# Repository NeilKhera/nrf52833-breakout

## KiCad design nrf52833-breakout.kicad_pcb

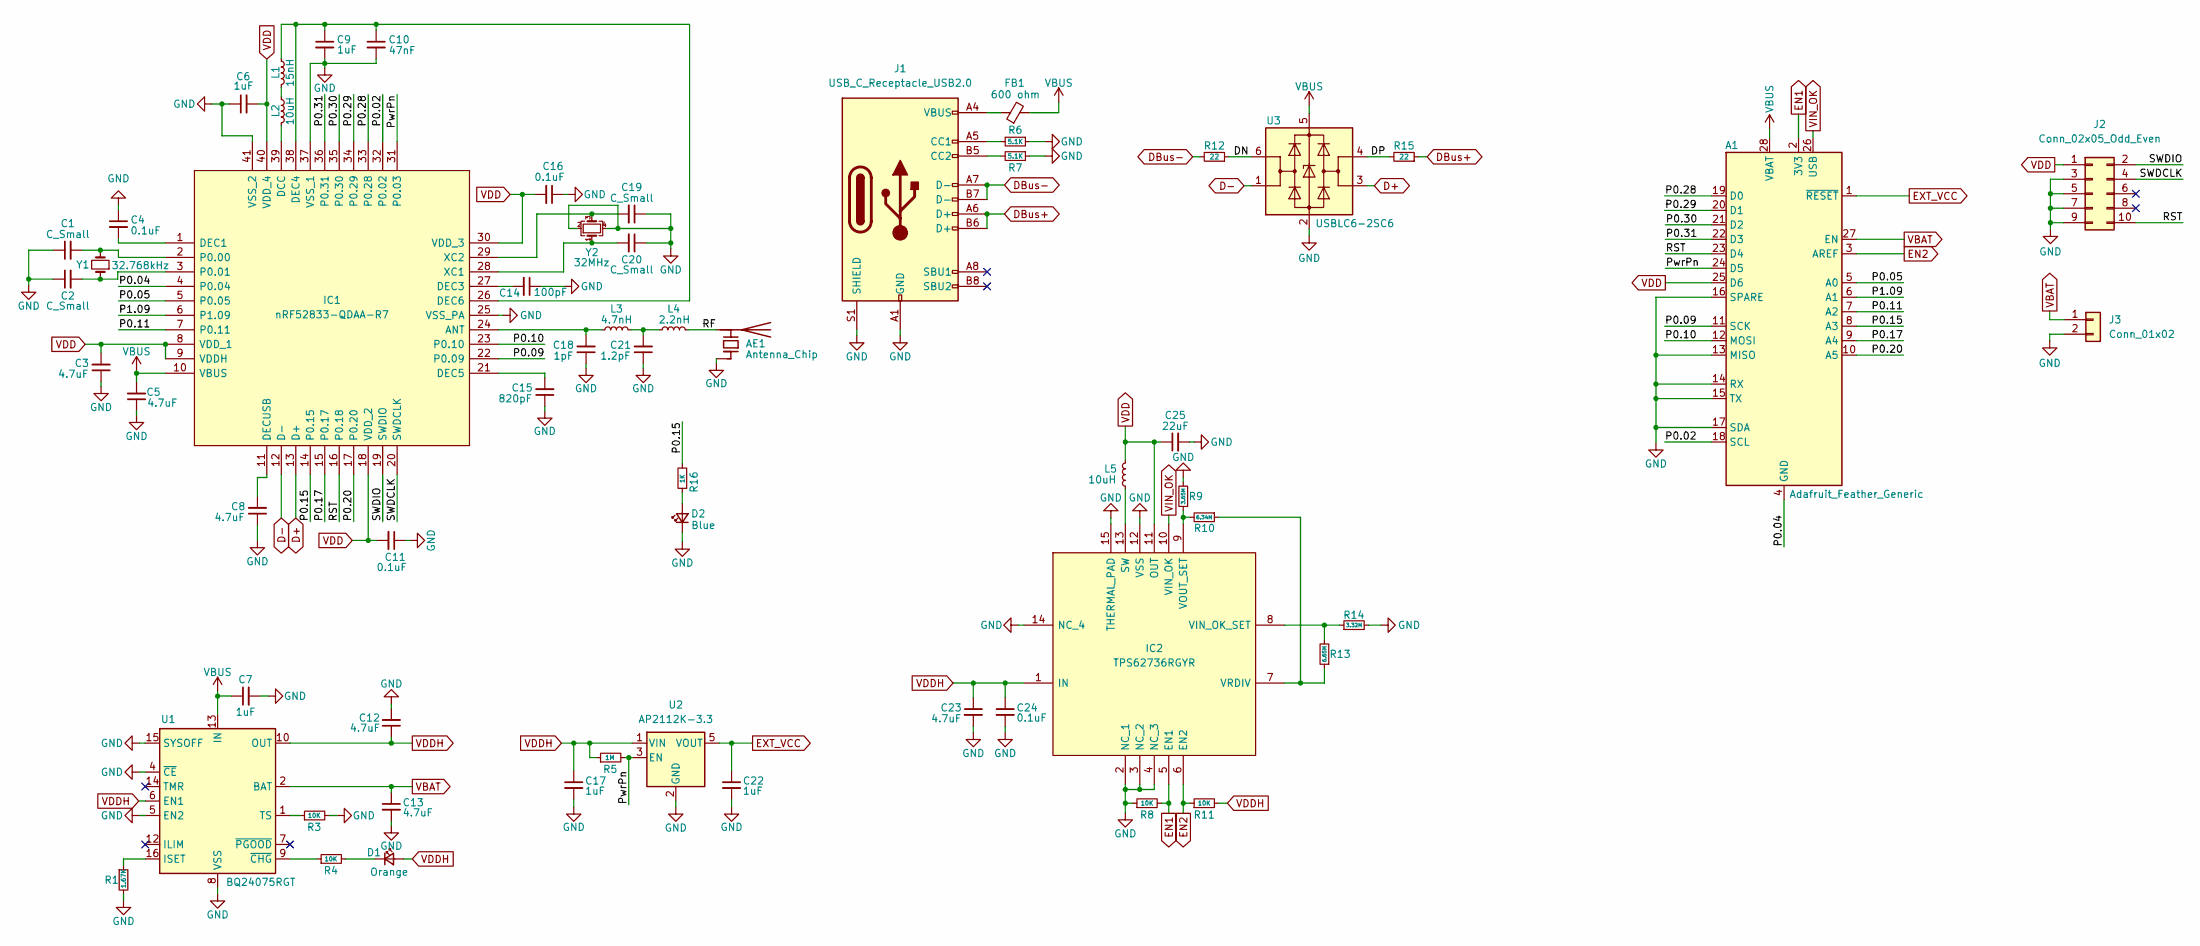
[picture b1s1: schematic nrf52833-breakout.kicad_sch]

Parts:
A1: Adafruit_Feather_Generic; Adafruit_Feather
AE1: Antenna_Chip; 2450AT42A100E
C1, C2, C19, C20: C_Small; C_0603_1608Metric
C3, C5, C8, C12, C13, C23: 4.7uF; C_0603_1608Metric
C4, C11, C16, C24: 0.1uF; C_0603_1608Metric
C6, C7, C9, C17, C22: 1uF; C_0603_1608Metric
C10: 47nF; C_0603_1608Metric
C14: 100pF; C_0603_1608Metric
C15: 820pF; C_0603_1608Metric
C18: 1pF; C_0402_1005Metric
C21: 1.2pF; C_0402_1005Metric
C25: 22uF; C_0603_1608Metric
D1: Orange; LED_0603_1608Metric
D2: Blue; LED_0603_1608Metric
FB1: 600 ohm; L_0603_1608Metric
IC1: nRF52833-QDAA-R7; QFN40P500X500X90-41N-D; Manufacturer_Part_Number nRF52833-QDAA-R7; Mouser Part Number 949-NRF52833-QDAA-R7
IC2: TPS62736RGYR; RGY_S-PVQFN-N14_; Manufacturer_Part_Number TPS62736RGYR; Mouser Part Number 595-TPS62736RGYR
J1: USB_C_Receptacle_USB2.0; USB_C_Receptacle_HRO_TYPE-C-31-M-12
J2: Conn_02x05_Odd_Even; 2X05_1.27MM_BOX_POSTS
J3: Conn_01x02; JSTPH2
L1: 15nH; L_0603_1608Metric
L2: 10uH; L_0603_1608Metric
L3: 4.7nH; L_0402_1005Metric
L4: 2.2nH; L_0402_1005Metric
L5: 10uH; L_1008_2520Metric
R1: 1.67K; R_0603_1608Metric
R3, R4, R8, R11: 10K; R_0603_1608Metric
R5: 1M; R_0603_1608Metric
R6, R7: 5.1K; R_0603_1608Metric
R9: 3.65M; R_0603_1608Metric
R10: 6.34M; R_0603_1608Metric
R12, R15: 22; R_0603_1608Metric
R13: 6.65M; R_0603_1608Metric
R14: 3.32M; R_0603_1608Metric
R16: 1K; R_0603_1608Metric
U1: BQ24075RGT; VQFN-16-1EP_3x3mm_P0.5mm_EP1.6x1.6mm
U2: AP2112K-3.3; SOT-23-5
U3: USBLC6-2SC6; SOT-23-6
Y1: 32.768kHz; Crystal_SMD_2012-2Pin_2.0x1.2mm_HandSoldering
Y2: 32MHz; Crystal_SMD_2520-4Pin_2.5x2.0mm

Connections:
/DN: R12.1, U3.6 (I/O1)
/DP: R15.2, U3.4 (I/O2)
/P0.02: A1.18 (SCL), IC1.32 (P0.02)
/P0.04: A1.4 (GND), IC1.4 (P0.04)
/P0.05: A1.5 (A0), IC1.5 (P0.05)
/P0.09: A1.11 (SCK), IC1.22 (P0.09)
/P0.10: A1.12 (MOSI), IC1.23 (P0.10)
/P0.11: A1.7 (A2), IC1.7 (P0.11)
/P0.15: A1.8 (A3), IC1.14 (P0.15), R16.2
/P0.17: A1.9 (A4), IC1.15 (P0.17)
/P0.20: A1.10 (A5), IC1.17 (P0.20)
/P0.28: A1.19 (D0), IC1.33 (P0.28)
/P0.29: A1.20 (D1), IC1.34 (P0.29)
/P0.30: A1.21 (D2), IC1.35 (P0.30)
/P0.31: A1.22 (D3), IC1.36 (P0.31)
/P1.09: A1.6 (A1), IC1.6 (P1.09)
/PwrPn: A1.24 (D5), IC1.31 (P0.03), R5.2, U2.3 (EN)
/RF: AE1.2 (PCB_Trace), L4.2
/RST: A1.23 (D4), IC1.16 (P0.18), J2.10
/SWDCLK: IC1.20 (SWDCLK), J2.4
/SWDIO: IC1.19 (SWDIO), J2.2
D+: IC1.13 (D+), U3.3 (I/O2)
D-: IC1.12 (D-), U3.1 (I/O1)
DBus+: J1.A6 (D+), J1.B6 (D+), R15.1
DBus-: J1.A7 (D-), J1.B7 (D-), R12.2
EN1: A1.2 (3V3), IC2.5 (EN1), R8.2
EN2: A1.3 (AREF), IC2.6 (EN2), R11.1
EXT_VCC: A1.1 (~RESET), C22.1, U2.5 (VOUT)
GND: A1.13 (MISO), A1.14 (RX), A1.15 (TX), A1.16 (SPARE), A1.17 (SDA), AE1.1 (FEED), C1.1, C2.1, C3.1, C4.1, C5.1, C6.1, C7.2, C8.1, C9.2, C10.2, C11.1, C12.2, C13.2, C14.1, C15.1, C16.1, C17.2, C18.1, C19.1, C20.1, C21.1, C22.2, C23.2, C24.2, C25.2, D2.1 (K), IC1.25 (VSS_PA), IC1.37 (VSS_1), IC1.41 (VSS_2), IC2.2 (NC_1), IC2.3 (NC_2), IC2.4 (NC_3), IC2.12 (VSS), IC2.14 (NC_4), IC2.15 (THERMAL_PAD), J1.A1 (GND), J1.A12 (GND), J1.B1 (GND), J1.B12 (GND), J1.S1 (SHIELD), J2.3, J2.5, J2.7, J2.9, J3.2, R1.2, R3.2, R6.1, R7.1, R8.1, R9.2, R14.2, U1.4 (~CE), U1.5 (EN2), U1.8 (VSS), U1.15 (SYSOFF), U1.17 (VSS), U2.2 (GND), U3.2 (GND), Y2.2, Y2.4
unnamed: C1.2, IC1.2 (P0.00), Y1.2
unnamed: C2.2, IC1.3 (P0.01), Y1.1
unnamed: C4.2, IC1.1 (DEC1)
unnamed: C8.2, IC1.11 (DECUSB)
unnamed: C9.1, C10.1, IC1.26 (DEC6), IC1.38 (DEC4), L1.1
unnamed: C14.2, IC1.27 (DEC3)
unnamed: C15.2, IC1.21 (DEC5)
unnamed: C18.2, IC1.24 (ANT), L3.1
unnamed: C19.2, IC1.29 (XC2), Y2.3
unnamed: C20.2, IC1.28 (XC1), Y2.1
unnamed: C21.2, L3.2, L4.1
unnamed: D1.1 (K), R4.2
unnamed: D2.2 (A), R16.1
unnamed: FB1.1, J1.A4 (VBUS), J1.A9 (VBUS), J1.B4 (VBUS), J1.B9 (VBUS)
unnamed: IC1.39 (DCC), L2.2
unnamed: IC2.7 (VRDIV), R10.1, R13.1
unnamed: IC2.8 (VIN_OK_SET), R13.2, R14.1
unnamed: IC2.9 (VOUT_SET), R9.1, R10.2
unnamed: IC2.13 (SW), L5.1
unnamed: J1.A5 (CC1), R6.2
unnamed: J1.B5 (CC2), R7.2
unnamed: L1.2, L2.1
unnamed: R1.1, U1.16 (ISET)
unnamed: R3.1, U1.1 (TS)
unnamed: R4.1, U1.9 (~CHG)
VBAT: A1.27 (EN), C13.1, J3.1, U1.2 (BAT), U1.3 (BAT)
VBUS: A1.28 (VBAT), C5.2, C7.1, FB1.2, IC1.10 (VBUS), U1.13 (IN), U3.5 (VBUS)
VDD: A1.25 (D6), C3.2, C6.2, C11.2, C16.2, C25.1, IC1.8 (VDD_1), IC1.9 (VDDH), IC1.18 (VDD_2), IC1.30 (VDD_3), IC1.40 (VDD_4), IC2.11 (OUT), J2.1, L5.2
VDDH: C12.1, C17.1, C23.1, C24.1, D1.2 (A), IC2.1 (IN), R5.1, R11.2, U1.6 (EN1), U1.10 (OUT), U1.11 (OUT), U2.1 (VIN)
VIN_OK: A1.26 (USB), IC2.10 (VIN_OK)

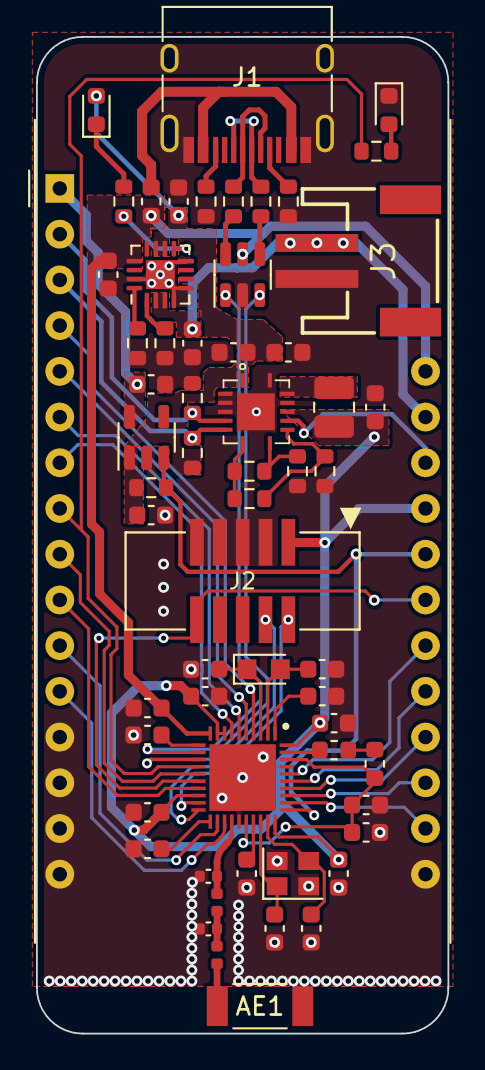
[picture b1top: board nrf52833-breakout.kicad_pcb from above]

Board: 2 copper layers, 22.9 x 55.4 mm, 60 parts (0 on the bottom side), 59 nets.

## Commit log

2023-06-20 File upload

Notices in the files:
parts and their libraries:
Copyright 2021 Accelerated Designs. All rights reserved.
